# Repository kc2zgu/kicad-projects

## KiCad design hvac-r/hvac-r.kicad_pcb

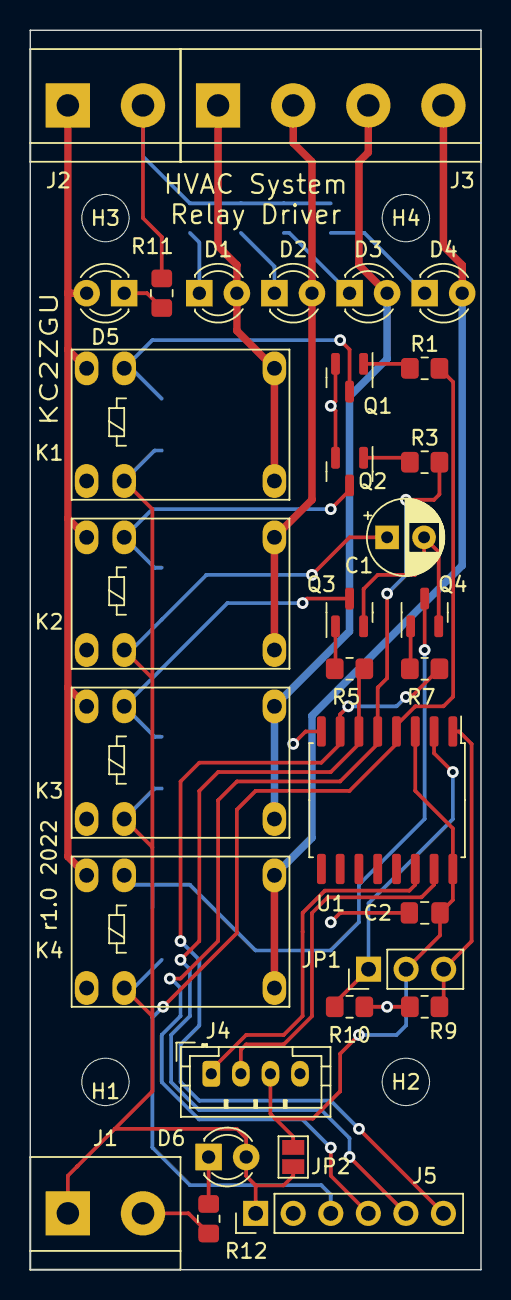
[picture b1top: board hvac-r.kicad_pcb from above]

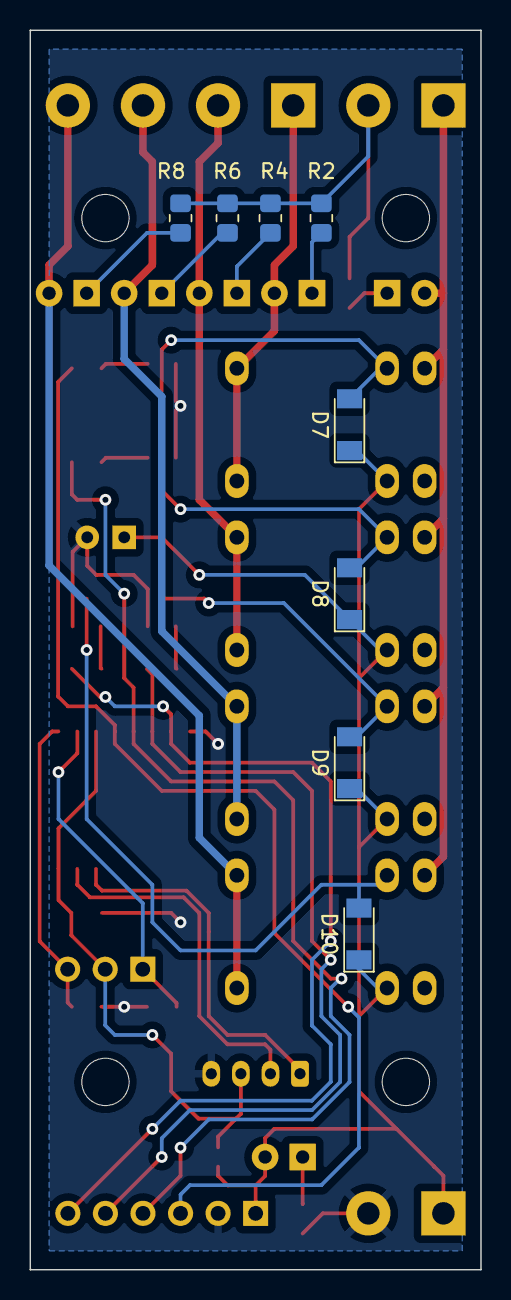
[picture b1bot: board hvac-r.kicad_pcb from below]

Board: 2 copper layers, 30.5 x 83.8 mm, 44 parts (8 on the bottom side), 31 nets.

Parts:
C1: 10uF; CP_Radial_D5.0mm_P2.50mm
C2: 1uF; C_0805_2012Metric_Pad1.18x1.45mm_HandSolder
D1, D2, D3, D4, D5, D6: LED; LED_D3.0mm
D7, D8, D9, D10: LL4148; D_MiniMELF
H1, H2, H3, H4: MountingHole; MountingHole_3.2mm_M3
J1, J2: Conn_01x02_Male; TerminalBlock_bornier-2_P5.08mm
J3: Conn_01x04_Male; TerminalBlock_bornier-4_P5.08mm
J4: Conn_01x04_Male; JST_PH_B4B-PH-K_1x04_P2.00mm_Vertical
J5: Conn_01x06_Male; PinHeader_1x06_P2.54mm_Vertical
JP1: Jumper_3_Open; PinHeader_1x03_P2.54mm_Vertical
JP2: SolderJumper_2_Open; SolderJumper-2_P1.3mm_Open_Pad1.0x1.5mm
K1, K2, K3, K4: J102-1C; Relay_SPDT_HJR-4102
Q1, Q2, Q3, Q4: MMBT3904; SOT-23
R1, R2, R3, R4, R5, R6, R7, R8, R9, R10, R11, R12: R_US; R_0805_2012Metric_Pad1.20x1.40mm_HandSolder
U1: TCA9554DW; SOIC-16W_7.5x10.3mm_P1.27mm

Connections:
+5V: C1.1, D6.2 (A), D7.1 (K), D8.1 (K), D9.1 (K), D10.1 (K), J1.1, J5.1, JP2.2 (B), K1.8, K2.8, K3.8, K4.8
/HVAC_1: D1.2 (A), J3.1, K1.1, K1.12
/HVAC_2: D2.2 (A), J3.2, K2.1, K2.12
/HVAC_3: D3.2 (A), J3.3, K3.1, K3.12
/HVAC_4: D4.2 (A), J3.4, K4.1, K4.12
/HVAC_C: J2.2, R2.2, R4.2, R6.2, R8.2, R11.1
/HVAC_V: D5.2 (A), J2.1, K1.6, K2.6, K3.6, K4.6
/SCL: J4.1, U1.14 (SCL)
/SDA: J4.2, U1.15 (SDA)
GND: C1.2, C2.2, J1.2, J4.4, J5.2, Q1.2 (E), Q2.2 (E), Q3.2 (E), Q4.2 (E), R9.2, R10.2, R12.2, U1.8 (GND)
unnamed: D1.1 (K), R2.1
unnamed: D2.1 (K), R4.1
unnamed: D3.1 (K), R6.1
unnamed: D4.1 (K), R8.1
unnamed: D5.1 (K), R11.2
unnamed: D6.1 (K), R12.1
unnamed: J5.5, R5.2, U1.6 (P2)
unnamed: J5.6, R7.2, U1.7 (P3)
unnamed: JP1.1 (A), R10.1, U1.2 (A1)
unnamed: JP1.3 (B), R9.1, U1.1 (A0)
unnamed: D7.2 (A), K1.5, Q1.3 (C)
unnamed: D8.2 (A), K2.5, Q2.3 (C)
unnamed: D9.2 (A), K3.5, Q3.3 (C)
unnamed: D10.2 (A), K4.5, Q4.3 (C)
unnamed: Q1.1 (B), R1.1
unnamed: Q2.1 (B), R3.1
unnamed: Q3.1 (B), R5.1
unnamed: Q4.1 (B), R7.1
unnamed: J5.3, R1.2, U1.4 (P0)
unnamed: J5.4, R3.2, U1.5 (P1)
VCC: C2.1, J4.3, JP1.2 (C), JP2.1 (A), U1.3 (A2), U1.16 (VDD)

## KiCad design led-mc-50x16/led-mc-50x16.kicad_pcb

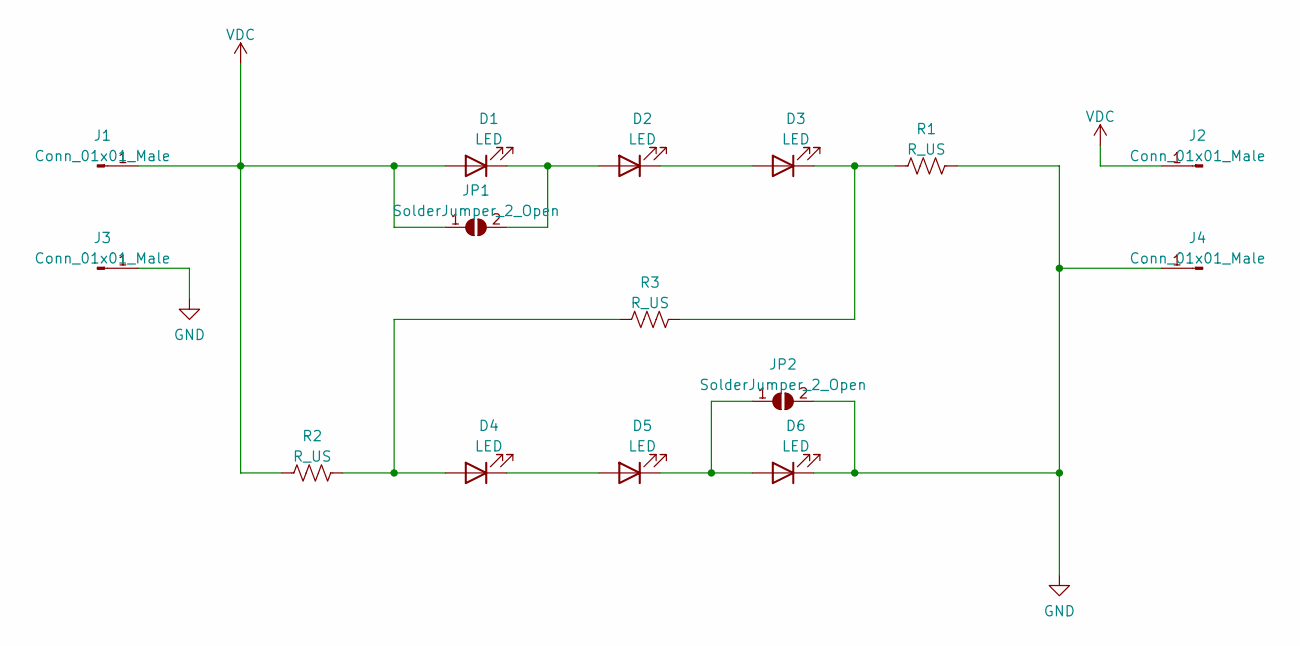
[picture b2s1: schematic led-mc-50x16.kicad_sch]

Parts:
D1, D2, D3, D4, D5, D6: LED; LED_PLCC_2835_Handsoldering
J1, J2, J3, J4: Conn_01x01_Male; TestPoint_Pad_3.0x3.0mm
JP1, JP2: SolderJumper_2_Open; SolderJumper-2_P1.3mm_Open_TrianglePad1.0x1.5mm
R1, R2, R3: R_US; R_1206_3216Metric_Pad1.30x1.75mm_HandSolder

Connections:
GND: D6.1 (K), J3.1, J4.1, JP2.2 (B), R1.2
unnamed: D1.1 (K), D2.2 (A), JP1.2 (B)
unnamed: D2.1 (K), D3.2 (A)
unnamed: D4.1 (K), D5.2 (A)
unnamed: D5.1 (K), D6.2 (A), JP2.1 (A)
unnamed: D3.1 (K), R1.1, R3.2
unnamed: D4.2 (A), R2.2, R3.1
VDC: D1.2 (A), J1.1, J2.1, JP1.1 (A), R2.1

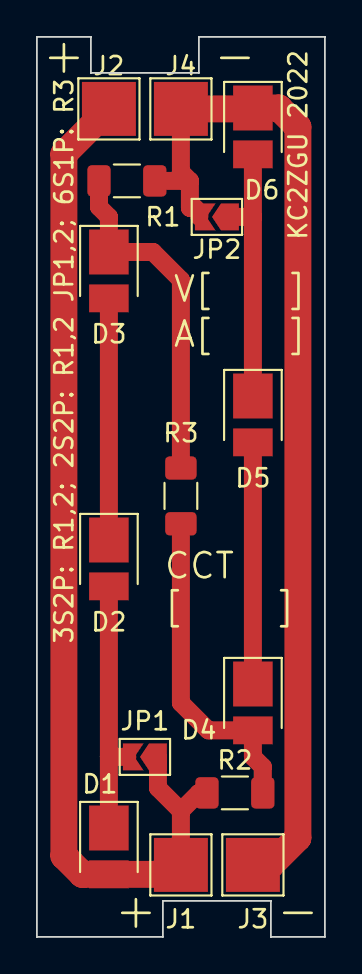
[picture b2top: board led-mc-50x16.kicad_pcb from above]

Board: 2 copper layers, 16.0 x 50.0 mm, 15 parts (0 on the bottom side), 8 nets.

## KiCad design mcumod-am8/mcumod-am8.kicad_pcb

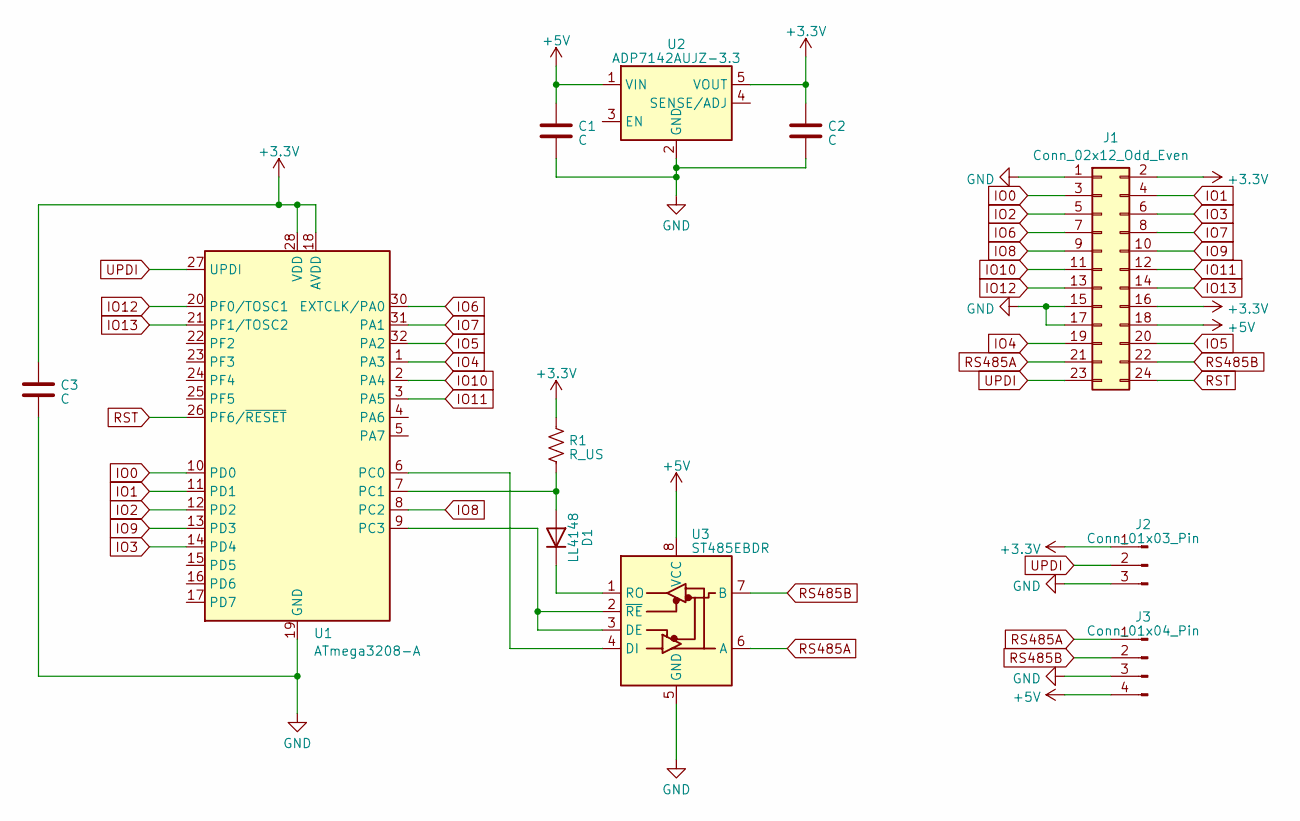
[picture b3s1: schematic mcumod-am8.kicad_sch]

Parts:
C1, C2, C3: C; C_0805_2012Metric_Pad1.18x1.45mm_HandSolder
D1: LL4148; D_MiniMELF
J1: Conn_02x12_Odd_Even; MCUMOD
J2: Conn_01x03_Pin; JST_ZH_B3B-ZR_1x03_P1.50mm_Vertical
J3: Conn_01x04_Pin; JST_PH_S4B-PH-SM4-TB_1x04-1MP_P2.00mm_Horizontal
R1: R_US; R_0805_2012Metric_Pad1.20x1.40mm_HandSolder
U1: ATmega3208-A; TQFP-32_7x7mm_P0.8mm
U2: ADP7142AUJZ-3.3; TSOT-23-5
U3: ST485EBDR; SOIC-8_3.9x4.9mm_P1.27mm

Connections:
+3.3V: C2.1, C3.1, J1.2, J1.16, J2.1, R1.2, U1.18 (AVDD), U1.28 (VDD), U2.5 (VOUT)
+5V: C1.1, J1.18, J3.4, U2.1 (VIN), U3.8 (VCC)
GND: C1.2, C2.2, C3.2, J1.1, J1.15, J1.17, J2.3, J3.3, U1.19 (GND), U1.29 (GND), U2.2 (GND), U3.5 (GND)
IO0: J1.3, U1.10 (PD0)
IO1: J1.4, U1.11 (PD1)
IO2: J1.5, U1.12 (PD2)
IO3: J1.6, U1.14 (PD4)
IO4: J1.19, U1.1 (PA3)
IO5: J1.20, U1.32 (PA2)
IO6: J1.7, U1.30 (EXTCLK/PA0)
IO7: J1.8, U1.31 (PA1)
IO8: J1.9, U1.8 (PC2)
IO9: J1.10, U1.13 (PD3)
IO10: J1.11, U1.2 (PA4)
IO11: J1.12, U1.3 (PA5)
IO12: J1.13, U1.20 (PF0/TOSC1)
IO13: J1.14, U1.21 (PF1/TOSC2)
unnamed: D1.2 (A), R1.1, U1.7 (PC1)
unnamed: D1.1 (K), U3.1 (RO)
unnamed: U1.6 (PC0), U3.4 (DI)
unnamed: U1.9 (PC3), U3.2 (~RE), U3.3 (DE)
RS485A: J1.21, J3.1, U3.6 (A)
RS485B: J1.22, J3.2, U3.7 (B)
RST: J1.24, U1.26 (PF6/~RESET)
UPDI: J1.23, J2.2, U1.27 (UPDI)

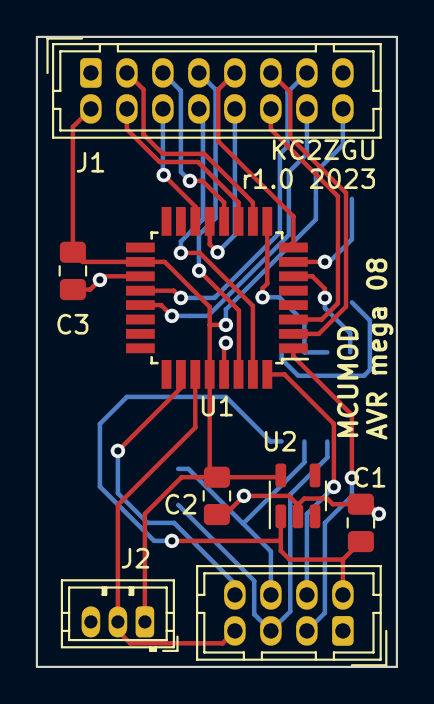
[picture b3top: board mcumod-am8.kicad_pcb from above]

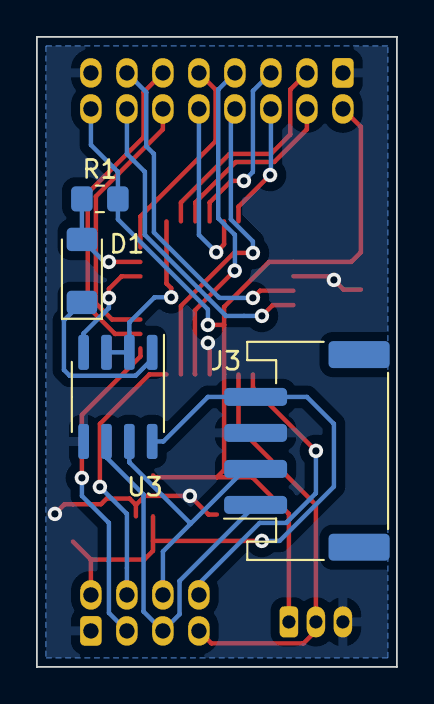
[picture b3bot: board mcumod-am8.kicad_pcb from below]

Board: 2 copper layers, 20.0 x 35.0 mm, 11 parts (4 on the bottom side), 25 nets.

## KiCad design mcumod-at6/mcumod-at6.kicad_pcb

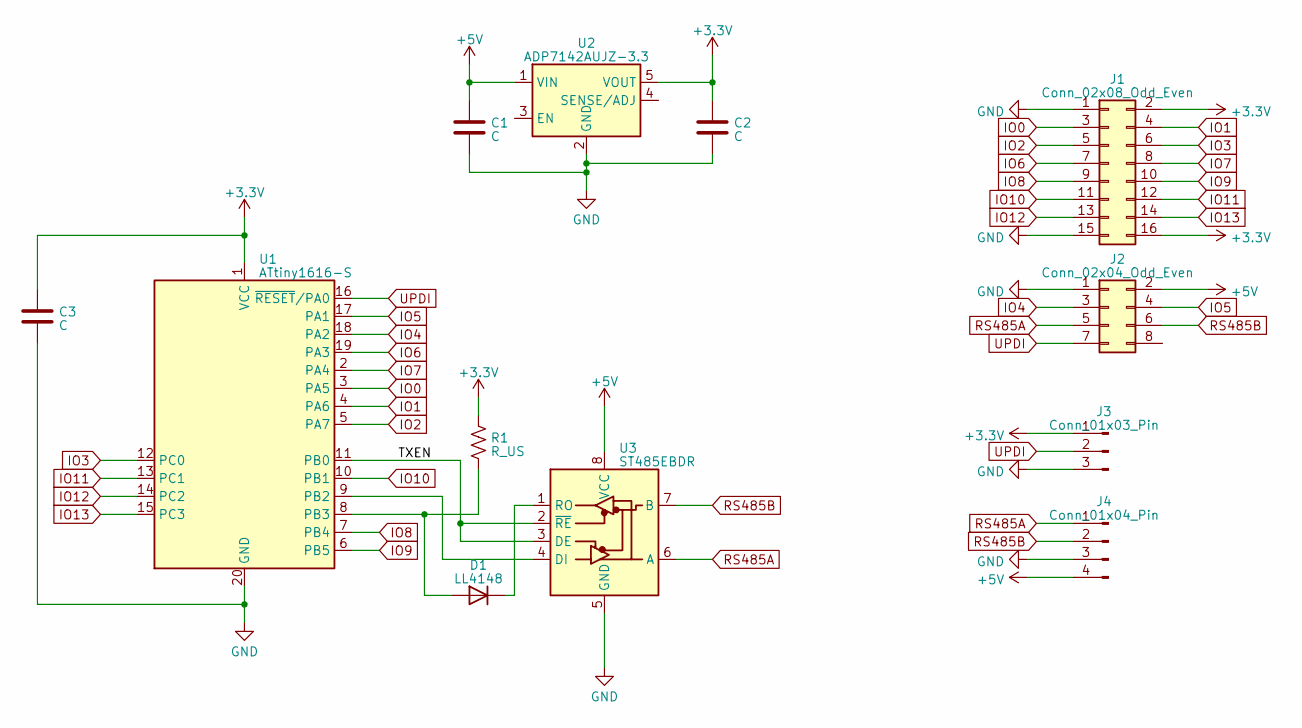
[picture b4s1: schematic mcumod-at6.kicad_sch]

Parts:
C1, C2, C3: C; C_0805_2012Metric_Pad1.18x1.45mm_HandSolder
D1: LL4148; D_MiniMELF
J1: Conn_02x08_Odd_Even; Hirose_DF11-16DP-2DSA_2x08_P2.00mm_Vertical
J2: Conn_02x04_Odd_Even; Hirose_DF11-8DP-2DSA_2x04_P2.00mm_Vertical
J3: Conn_01x03_Pin; JST_ZH_B3B-ZR_1x03_P1.50mm_Vertical
J4: Conn_01x04_Pin; JST_PH_S4B-PH-SM4-TB_1x04-1MP_P2.00mm_Horizontal
R1: R_US; R_0805_2012Metric_Pad1.20x1.40mm_HandSolder
U1: ATtiny1616-S; SOIC-20W_7.5x12.8mm_P1.27mm
U2: ADP7142AUJZ-3.3; TSOT-23-5
U3: ST485EBDR; SOIC-8_3.9x4.9mm_P1.27mm

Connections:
+3.3V: C2.1, C3.1, J1.2, J1.16, J3.1, R1.2, U1.1 (VCC), U2.5 (VOUT)
+5V: C1.1, J2.2, J4.4, U2.1 (VIN), U3.8 (VCC)
/TXEN: U1.11 (PB0), U3.2 (~RE), U3.3 (DE)
GND: C1.2, C2.2, C3.2, J1.1, J1.15, J2.1, J3.3, J4.3, U1.20 (GND), U2.2 (GND), U3.5 (GND)
IO0: J1.3, U1.3 (PA5)
IO1: J1.4, U1.4 (PA6)
IO2: J1.5, U1.5 (PA7)
IO3: J1.6, U1.12 (PC0)
IO4: J2.3, U1.18 (PA2)
IO5: J2.4, U1.17 (PA1)
IO6: J1.7, U1.19 (PA3)
IO7: J1.8, U1.2 (PA4)
IO8: J1.9, U1.7 (PB4)
IO9: J1.10, U1.6 (PB5)
IO10: J1.11, U1.10 (PB1)
IO11: J1.12, U1.13 (PC1)
IO12: J1.13, U1.14 (PC2)
IO13: J1.14, U1.15 (PC3)
unnamed: D1.2 (A), R1.1, U1.8 (PB3)
unnamed: D1.1 (K), U3.1 (RO)
unnamed: U1.9 (PB2), U3.4 (DI)
RS485A: J2.5, J4.1, U3.6 (A)
RS485B: J2.6, J4.2, U3.7 (B)
UPDI: J2.7, J3.2, U1.16 (~RESET/PA0)

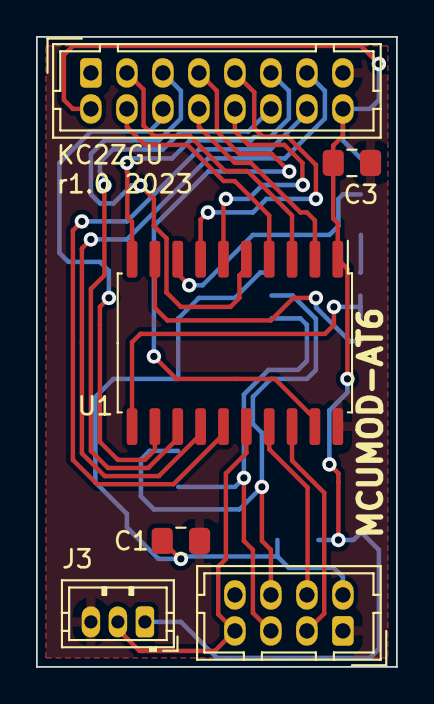
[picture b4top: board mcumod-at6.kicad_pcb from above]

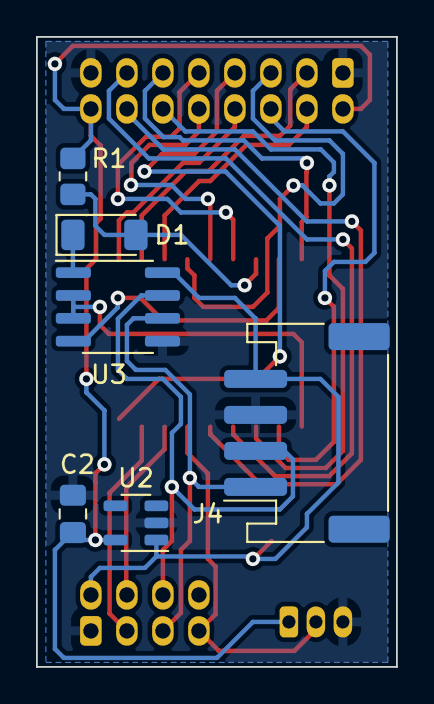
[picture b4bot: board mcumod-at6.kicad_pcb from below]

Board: 2 copper layers, 20.0 x 35.0 mm, 12 parts (6 on the bottom side), 24 nets.

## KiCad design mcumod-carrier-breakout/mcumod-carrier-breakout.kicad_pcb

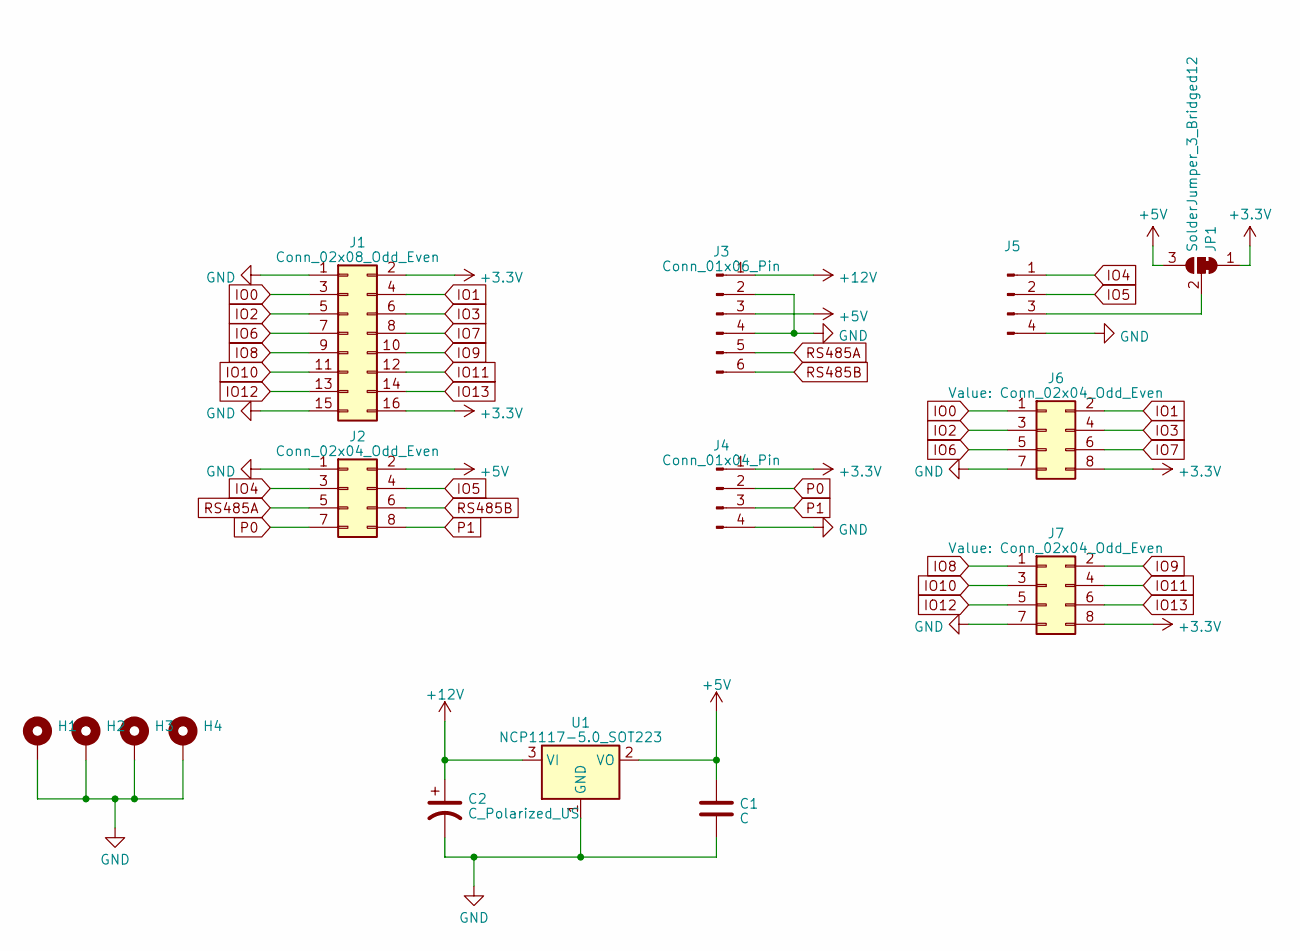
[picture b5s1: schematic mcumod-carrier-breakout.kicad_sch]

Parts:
C1: C; C_1210_3225Metric_Pad1.33x2.70mm_HandSolder
C2: C_Polarized_US; CP_Radial_D5.0mm_P2.50mm
H1, H2, H3, H4: MountingHole_Pad; MountingHole_3.2mm_M3_DIN965_Pad
J1: Conn_02x08_Odd_Even; Hirose_DF11-16DP-2DSA_2x08_P2.00mm_Vertical
J2: Conn_02x04_Odd_Even; Hirose_DF11-8DP-2DSA_2x04_P2.00mm_Vertical
J3: Conn_01x06_Pin; PinHeader_1x06_P2.54mm_Vertical
J4: Conn_01x04_Pin; JST_ZH_B4B-ZR_1x04_P1.50mm_Vertical
J5: Conn_01x04_Male; JST_PH_B4B-PH-K_1x04_P2.00mm_Vertical
J6, J7: Conn_02x04_Odd_Even; PinHeader_2x04_P2.54mm_Vertical
JP1: SolderJumper_3_Bridged12; SolderJumper-3_P1.3mm_Bridged12_Pad1.0x1.5mm
U1: NCP1117-5.0_SOT223; SOT-223-3_TabPin2

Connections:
+3.3V: J1.2, J1.16, J4.1, J6.8, J7.8, JP1.1 (A)
+5V: C1.1, J2.2, J3.3, JP1.3 (B), U1.2 (VO)
+12V: C2.1, J3.1, U1.3 (VI)
GND: C1.2, C2.2, H1.1, H2.1, H3.1, H4.1, J1.1, J1.15, J2.1, J3.2, J3.4, J4.4, J5.4, J6.7, J7.7, U1.1 (GND)
IO0: J1.3, J6.1
IO1: J1.4, J6.2
IO2: J1.5, J6.3
IO3: J1.6, J6.4
IO4: J2.3, J5.1
IO5: J2.4, J5.2
IO6: J1.7, J6.5
IO7: J1.8, J6.6
IO8: J1.9, J7.1
IO9: J1.10, J7.2
IO10: J1.11, J7.3
IO11: J1.12, J7.4
IO12: J1.13, J7.5
IO13: J1.14, J7.6
unnamed: J5.3, JP1.2 (C)
P0: J2.7, J4.2
P1: J2.8, J4.3
RS485A: J2.5, J3.5
RS485B: J2.6, J3.6

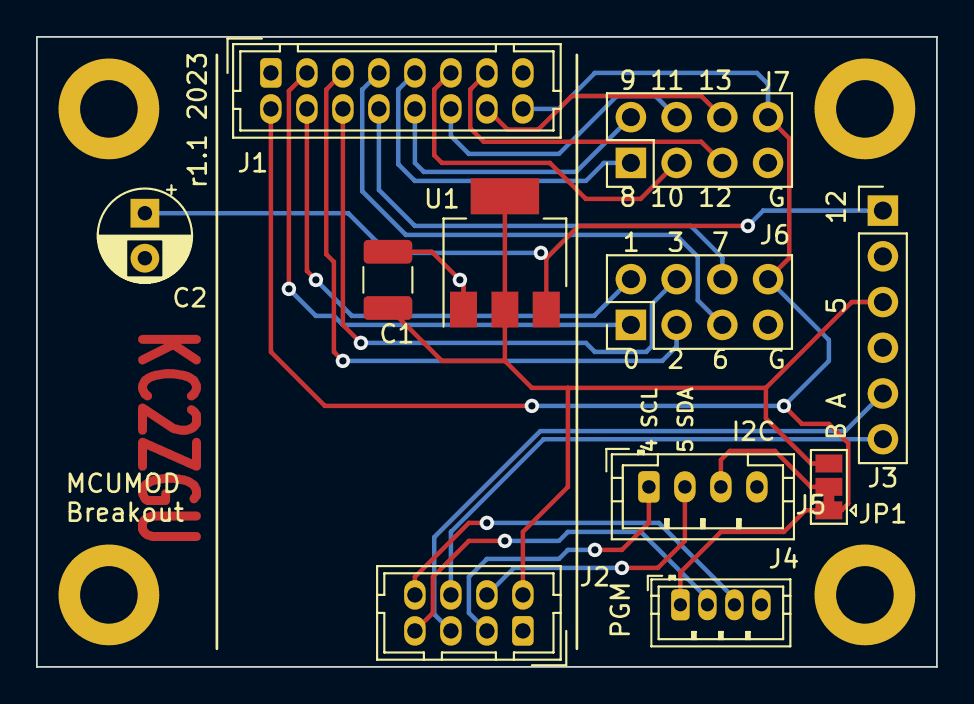
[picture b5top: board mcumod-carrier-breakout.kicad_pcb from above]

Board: 2 copper layers, 50.0 x 35.0 mm, 15 parts (0 on the bottom side), 23 nets.

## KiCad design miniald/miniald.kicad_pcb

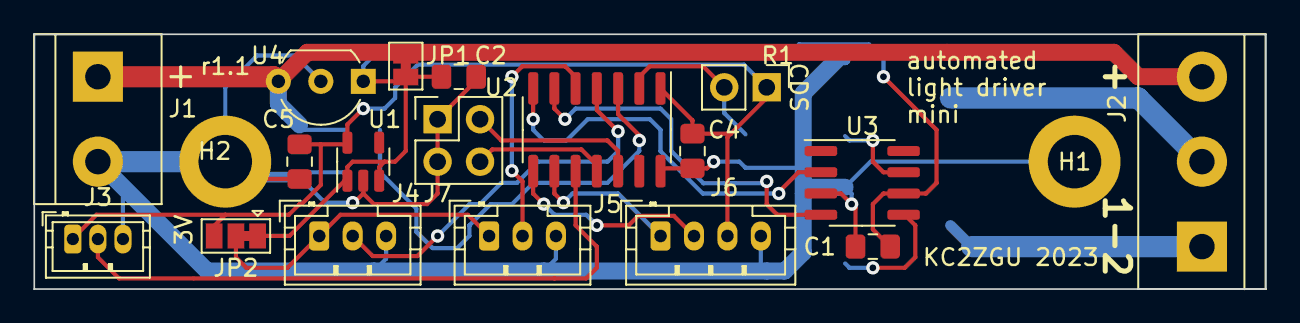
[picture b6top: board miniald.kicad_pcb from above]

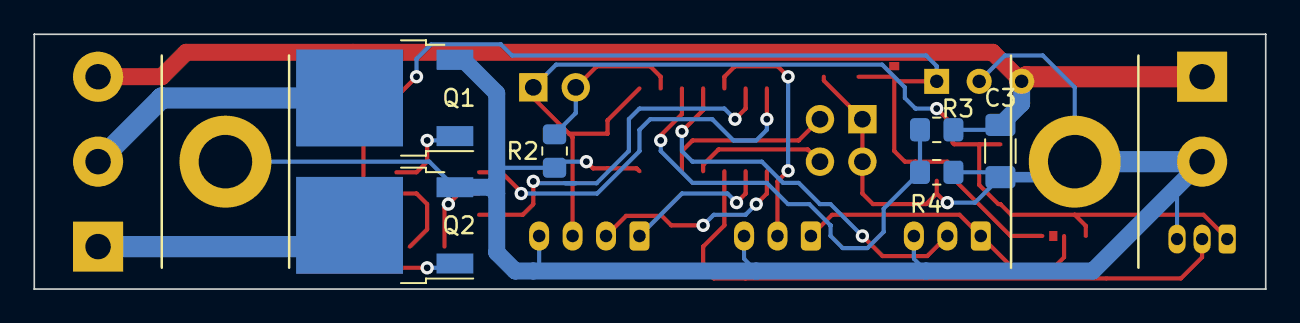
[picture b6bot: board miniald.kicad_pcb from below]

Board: 2 copper layers, 73.7 x 15.2 mm, 26 parts (6 on the bottom side), 20 nets.

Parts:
C1, C2, C4, C5: C; C_0805_2012Metric_Pad1.18x1.45mm_HandSolder
C3: C; C_1206_3216Metric_Pad1.33x1.80mm_HandSolder
H1, H2: MountingHole_Pad; MountingHole_3.2mm_M3_ISO14580_Pad
J1: Conn_01x02_Male; TerminalBlock_bornier-2_P5.08mm
J2: Conn_01x03_Male; TerminalBlock_bornier-3_P5.08mm
J3: Conn_01x03_Pin; JST_ZH_B3B-ZR_1x03_P1.50mm_Vertical
J4, J5: Conn_01x03_Male; JST_PH_B3B-PH-K_1x03_P2.00mm_Vertical
J6: Conn_01x04_Male; JST_PH_B4B-PH-K_1x04_P2.00mm_Vertical
J7: Conn_01x04_Male; PinHeader_2x02_P2.54mm_Vertical
JP1: SolderJumper_2_Bridged; SolderJumper-2_P1.3mm_Bridged_Pad1.0x1.5mm
JP2: SolderJumper_3_Bridged12; SolderJumper-3_P1.3mm_Bridged12_Pad1.0x1.5mm
Q1, Q2: Q_NMOS_GDS; TO-252-2
R1: R_Photo; PinHeader_1x02_P2.54mm_Vertical
R2, R3, R4: R_US; R_0805_2012Metric_Pad1.20x1.40mm_HandSolder
U1: ADP7142AUJZ-3.3; TSOT-23-5
U2: ATtiny804-SS; SOIC-14_3.9x8.7mm_P1.27mm
U3: MIC4427; SOIC-8_3.9x4.9mm_P1.27mm
U4: L78L05_TO92; TO-92_Inline_Wide

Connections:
+3.3V: C4.1, C5.1, J3.1, J6.3, JP2.3 (B), R1.1, U1.5 (VOUT), U2.1 (VCC)
+5V: C1.1, C2.1, JP1.2 (B), JP2.1 (A), U1.1 (VIN), U1.3 (EN), U3.6 (V+), U4.1 (VO)
+BATT: C3.1, J1.1, J2.3, JP1.1 (A), R3.1, U4.3 (VI)
CDS: R1.2, R2.1, U2.2 (PA4)
GND: C1.2, C2.2, C3.2, C4.2, C5.2, H1.1, H2.1, J1.2, J3.3, J4.3, J5.3, J6.4, J7.1, J7.3, Q1.3 (S), Q2.3 (S), R2.2, R4.2, U1.2 (GND), U2.14 (GND), U3.3 (GND), U4.2 (GND)
IO0: J7.4, U2.11 (PA1)
IO1: J7.2, U2.12 (PA2)
unnamed: J2.1, Q2.2 (D)
unnamed: J2.2, Q1.2 (D)
unnamed: J4.1, J5.1, JP2.2 (C)
unnamed: J4.2, U2.4 (PA6)
unnamed: J5.2, U2.5 (PA7)
unnamed: Q1.1 (G), U3.7 (OUT_A)
unnamed: Q2.1 (G), U3.5 (OUT_B)
unnamed: R3.2, R4.1, U2.3 (PA5)
PWM1: U2.7 (PB2), U3.2 (IN_A)
PWM2: U2.6 (PB3), U3.4 (IN_B)
SCL: J6.1, U2.9 (PB0)
SDA: J6.2, U2.8 (PB1)
UPDI: J3.2, U2.10 (~RESET/PA0)

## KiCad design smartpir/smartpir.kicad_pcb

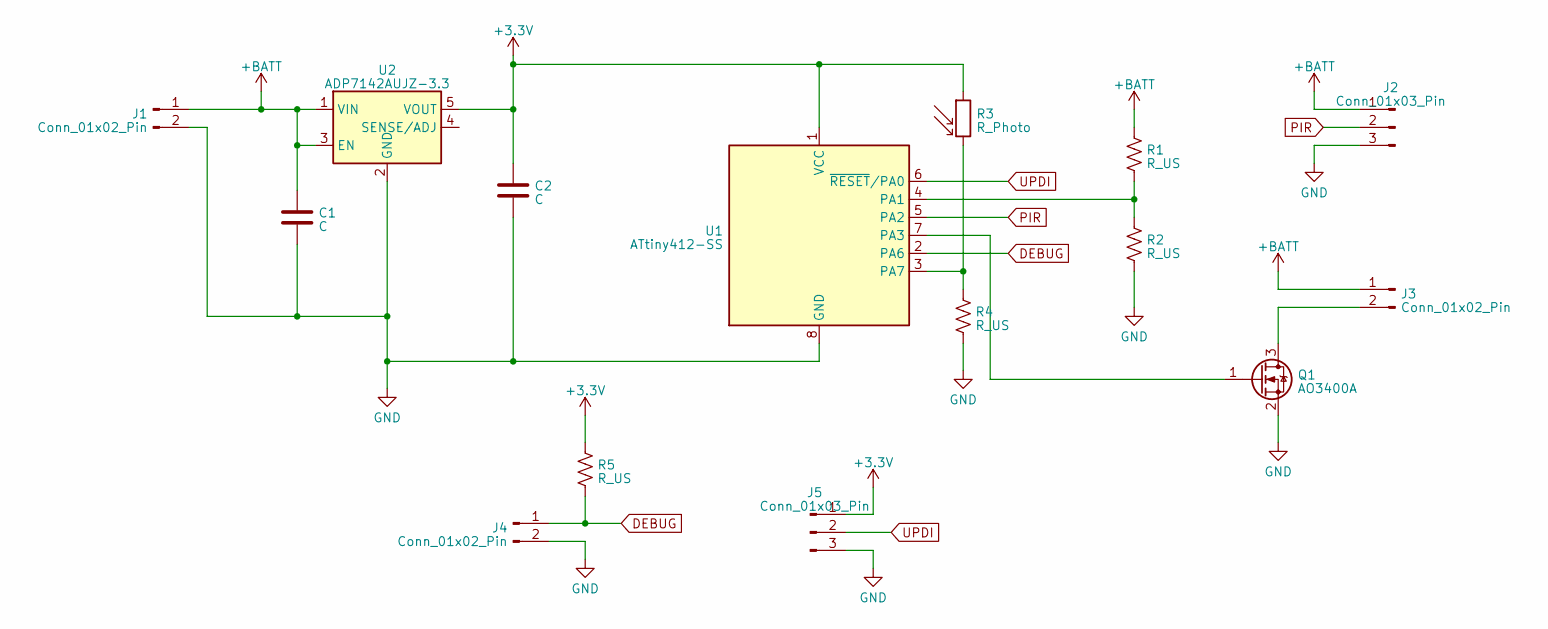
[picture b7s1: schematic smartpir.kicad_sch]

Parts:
C1, C2: C; C_0805_2012Metric_Pad1.18x1.45mm_HandSolder
J1, J3, J4: Conn_01x02_Pin; PinHeader_1x02_P2.00mm_Vertical
J2: Conn_01x03_Pin; PinHeader_1x03_P2.54mm_Vertical
J5: Conn_01x03_Pin; JST_ZH_B3B-ZR_1x03_P1.50mm_Vertical
Q1: AO3400A; SOT-23
R1, R2, R4, R5: R_US; R_0805_2012Metric_Pad1.20x1.40mm_HandSolder
R3: R_Photo; R_Axial_DIN0204_L3.6mm_D1.6mm_P2.54mm_Vertical
U1: ATtiny412-SS; SOIC-8_3.9x4.9mm_P1.27mm
U2: ADP7142AUJZ-3.3; TSOT-23-5

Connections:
+3.3V: C2.1, J5.1, R3.1, R5.1, U1.1 (VCC), U2.5 (VOUT)
+BATT: C1.1, J1.1, J2.1, J3.1, R1.1, U2.1 (VIN), U2.3 (EN)
DEBUG: J4.1, R5.2, U1.2 (PA6)
GND: C1.2, C2.2, J1.2, J2.3, J4.2, J5.3, Q1.2 (S), R2.2, R4.2, U1.8 (GND), U2.2 (GND)
unnamed: J3.2, Q1.3 (D)
unnamed: Q1.1 (G), U1.7 (PA3)
unnamed: R1.2, R2.1, U1.4 (PA1)
unnamed: R3.2, R4.1, U1.3 (PA7)
PIR: J2.2, U1.5 (PA2)
UPDI: J5.2, U1.6 (~RESET/PA0)

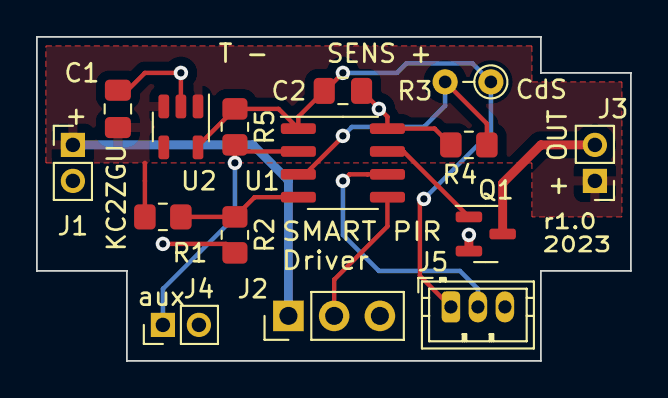
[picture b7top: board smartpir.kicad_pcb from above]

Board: 2 copper layers, 33.0 x 18.0 mm, 15 parts (0 on the bottom side), 10 nets.

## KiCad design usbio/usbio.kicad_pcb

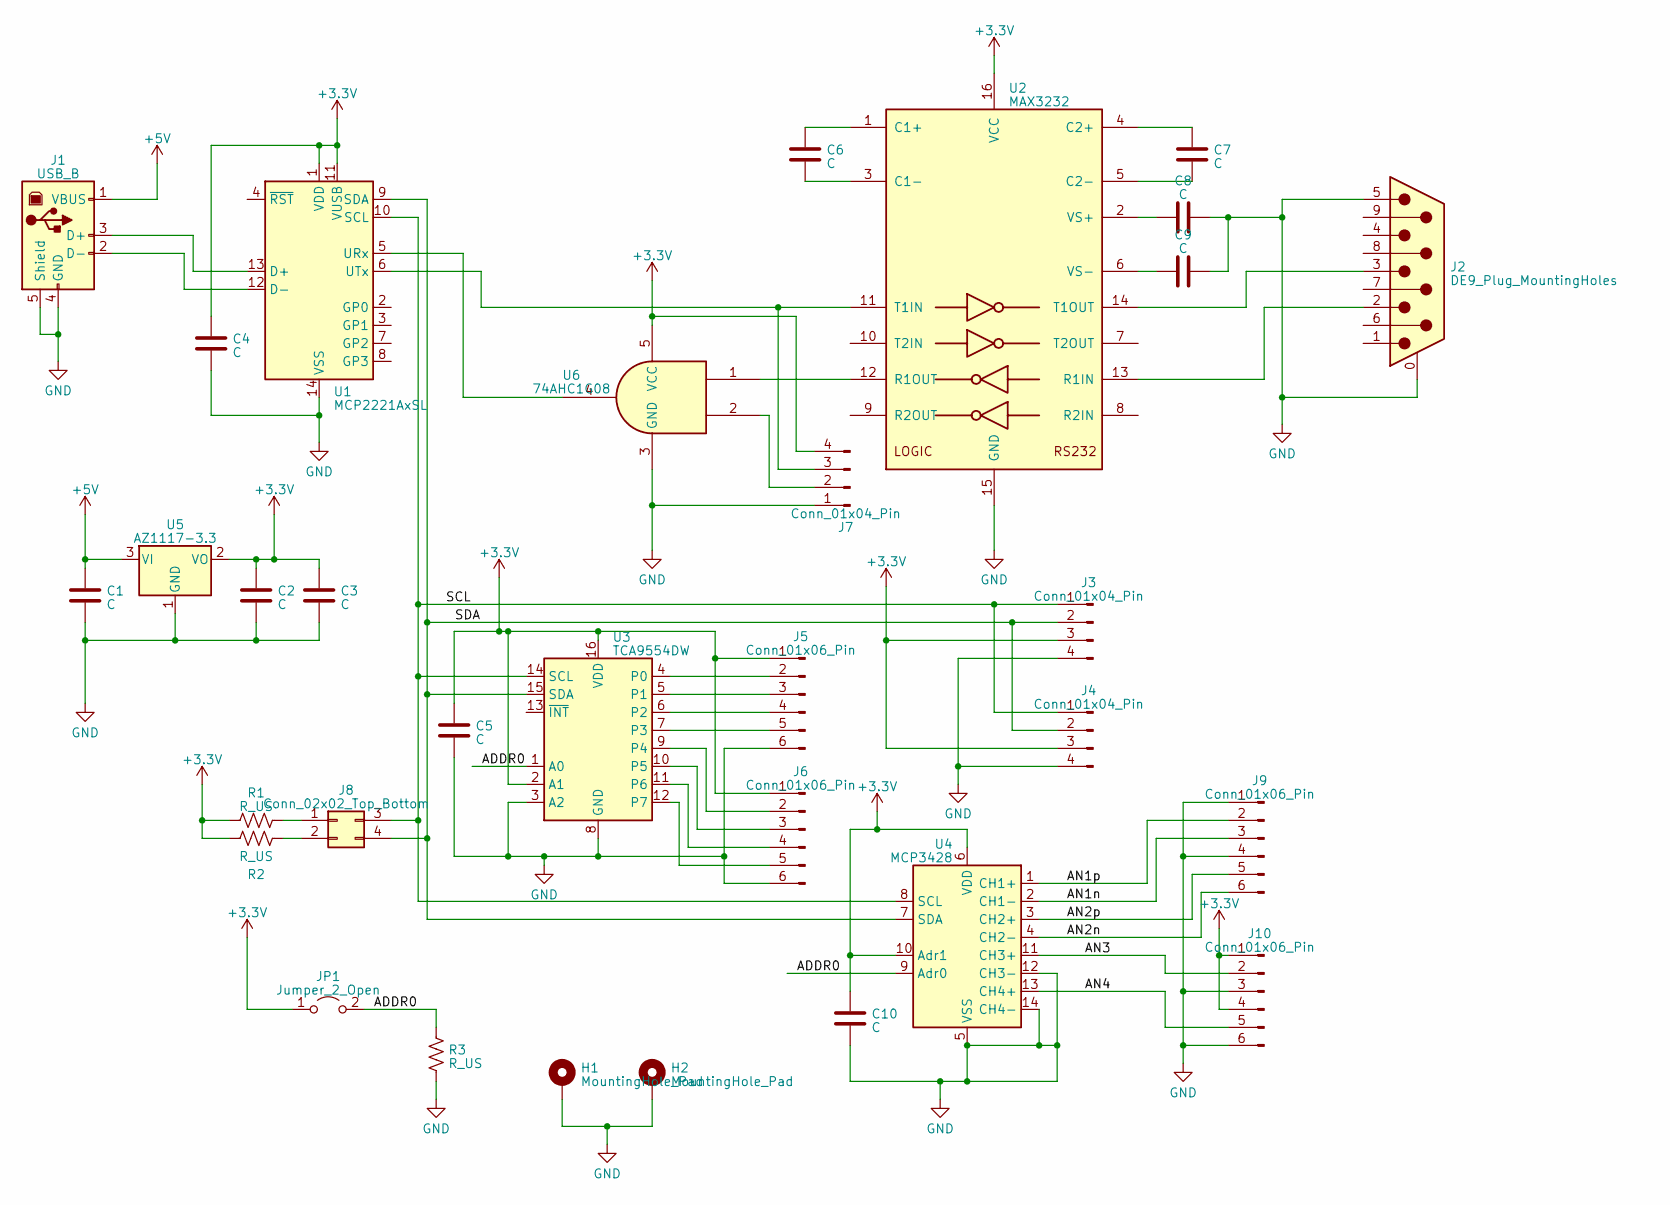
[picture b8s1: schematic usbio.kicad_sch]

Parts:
C1, C2: C; C_1210_3225Metric
C3: C; C_1206_3216Metric
C4, C5, C6, C7, C8, C9, C10: C; C_0805_2012Metric
H1, H2: MountingHole_Pad; MountingHole_3.2mm_M3_DIN965_Pad
J1: USB_B; USB_B_OST_USB-B1HSxx_Horizontal
J2: DE9_Plug_MountingHoles; DSUB-9_Male_Vertical_P2.77x2.84mm_MountingHoles
J3, J4: Conn_01x04_Pin; JST_PH_B4B-PH-K_1x04_P2.00mm_Vertical
J5, J6, J9, J10: Conn_01x06_Pin; PinHeader_1x06_P2.54mm_Vertical
J7: Conn_01x04_Pin; PinHeader_1x04_P2.54mm_Vertical
J8: Conn_02x02_Top_Bottom; PinHeader_2x02_P2.00mm_Vertical
JP1: Jumper_2_Open; PinHeader_1x02_P2.00mm_Vertical
R1, R2, R3: R_US; R_0805_2012Metric
U1: MCP2221AxSL; SOIC-14_3.9x8.7mm_P1.27mm
U2: MAX3232; SOIC-16_3.9x9.9mm_P1.27mm
U3: TCA9554DW; SOIC-16W_7.5x10.3mm_P1.27mm
U4: MCP3428; SOIC-14_3.9x8.7mm_P1.27mm
U5: AZ1117-3.3; SOT-89-3_Handsoldering
U6: 74AHC1G08; SOT-23-5_HandSoldering

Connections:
+3.3V: C2.1, C3.1, C4.1, C5.1, C10.1, J3.3, J4.3, J5.1, J6.1, J7.4, J10.1, J10.4, JP1.1 (A), R1.1, R2.1, U1.1 (VDD), U1.11 (VUSB), U2.16 (VCC), U3.2 (A1), U3.16 (VDD), U4.6 (VDD), U4.10 (Adr1), U5.2 (VO), U6.5 (VCC)
+5V: C1.1, J1.1 (VBUS), U5.3 (VI)
/ADDR0: JP1.2 (B), R3.2, U3.1 (A0), U4.9 (Adr0)
/AN1n: J9.3, U4.2 (CH1-)
/AN1p: J9.2, U4.1 (CH1+)
/AN2n: J9.6, U4.4 (CH2-)
/AN2p: J9.5, U4.3 (CH2+)
/AN3: J10.2, U4.11 (CH3+)
/AN4: J10.5, U4.13 (CH4+)
/SCL: J3.1, J4.1, J8.3, U1.10 (SCL), U3.14 (SCL), U4.8 (SCL)
/SDA: J3.2, J4.2, J8.4, U1.9 (SDA), U3.15 (SDA), U4.7 (SDA)
GND: C1.2, C2.2, C3.2, C4.2, C5.2, C8.2, C9.2, C10.2, H1.1, H2.1, J1.4 (GND), J1.5 (Shield), J2.0 (PAD), J2.5, J3.4, J4.4, J5.6, J6.6, J7.1, J9.1, J9.4, J10.3, J10.6, R3.1, U1.14 (VSS), U2.15 (GND), U3.3 (A2), U3.8 (GND), U4.5 (VSS), U4.12 (CH3-), U4.14 (CH4-), U5.1 (GND), U6.3 (GND)
unnamed: J1.3 (D+), U1.13 (D+)
unnamed: J1.2 (D-), U1.12 (D-)
unnamed: J5.2, U3.4 (P0)
unnamed: J5.3, U3.5 (P1)
unnamed: J5.4, U3.6 (P2)
unnamed: J5.5, U3.7 (P3)
unnamed: J6.2, U3.9 (P4)
unnamed: J6.3, U3.10 (P5)
unnamed: J6.4, U3.11 (P6)
unnamed: J6.5, U3.12 (P7)
unnamed: J7.2, U6.2
unnamed: J7.3, U1.6 (UTx), U2.11 (T1IN)
unnamed: J8.1, R1.2
unnamed: J8.2, R2.2
unnamed: U1.5 (URx), U6.4
unnamed: C6.1, U2.1 (C1+)
unnamed: C6.2, U2.3 (C1-)
unnamed: C7.1, U2.4 (C2+)
unnamed: C7.2, U2.5 (C2-)
unnamed: J2.2, U2.13 (R1IN)
unnamed: U2.12 (R1OUT), U6.1
unnamed: J2.3, U2.14 (T1OUT)
unnamed: C8.1, U2.2 (VS+)
unnamed: C9.1, U2.6 (VS-)

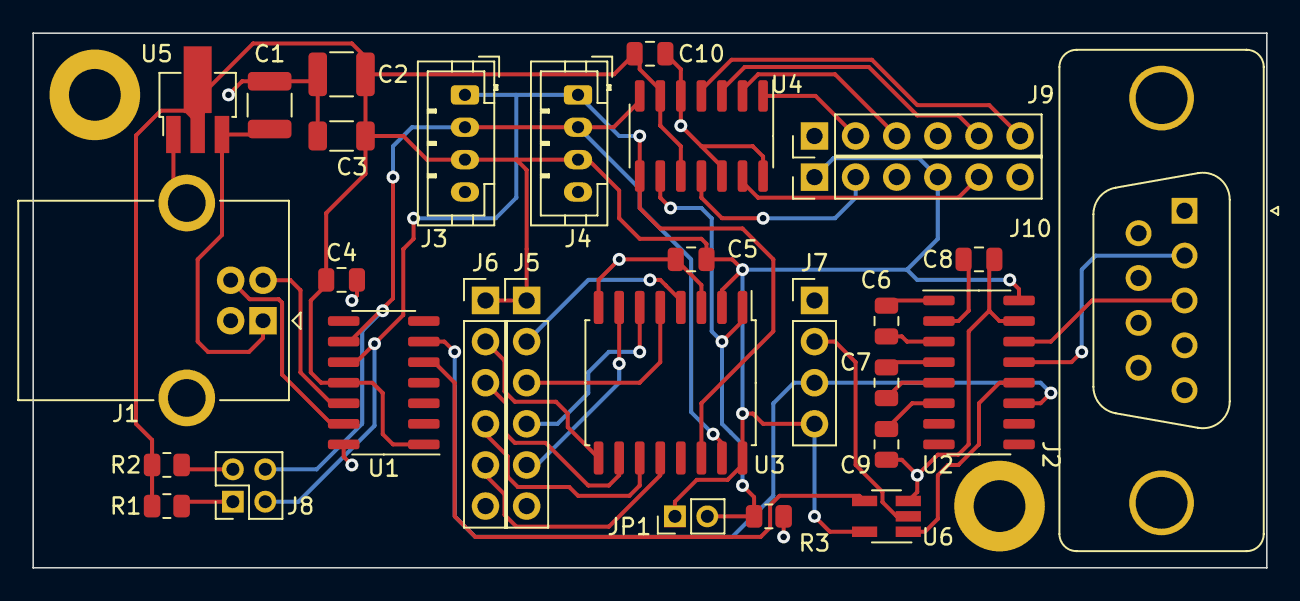
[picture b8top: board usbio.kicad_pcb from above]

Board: 2 copper layers, 76.2 x 33.0 mm, 32 parts (0 on the bottom side), 36 nets.
